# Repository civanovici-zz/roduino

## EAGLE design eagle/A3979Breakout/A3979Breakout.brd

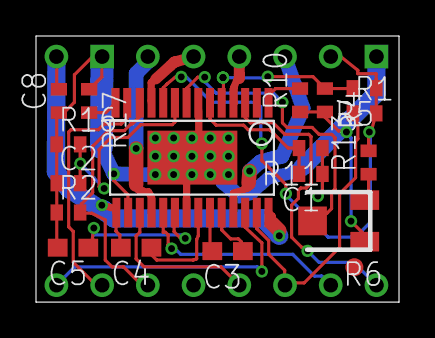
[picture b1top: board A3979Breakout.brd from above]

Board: 2 copper layers, 20.2 x 14.8 mm, 19 parts (0 on the bottom side), 25 nets.

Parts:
C1, C2: 680pF; C0402
C3, C4, C5: 0.22uF; C0603
C8: 0.1uF; C0402
E$1: FIDUCIAL_L10
IC1: A3979; TSSOP28
R1, R2, R5: 100K; R0402
R4: 47K; R0402
R6: RTRIM22AR
R10, R17: 0.2; R0402
R11, R16: 20K; R0402
R13: 2.7K; R0402
U$1: POLOLU_A4983CARRIER; A3979BREAKOUT

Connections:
1A: IC1.P$4, U$1.1A
1B: IC1.P$25, U$1.1B
2A: IC1.P$11, U$1.2A
2B: IC1.P$18, U$1.2B
+12V: C4.2, C8.2, IC1.P$15, IC1.P$28, U$1.VMOT
DIR: IC1.P$3, U$1.DIR
EN: IC1.P$26, U$1.EN
GND: C1.1, C2.1, C5.2, C8.1, IC1.P$7, IC1.P$16, IC1.P$21, IC1.P$29, R2.1, R4.2, R6.1, R10.1, R11.1, R16.1, R17.1, U$1.GND, U$1.GND@0
MS1: IC1.P$13, U$1.MS1
MS2: IC1.P$12, R2.2, U$1.MS2
unnamed: IC1.P$1, R10.2
unnamed: R6.3, R13.1
unnamed: IC1.P$14, R17.2
unnamed: IC1.P$5, R4.1, R5.2
unnamed: IC1.P$8, R6.2
unnamed: C1.2, IC1.P$6, R11.2
unnamed: C2.2, IC1.P$9, R16.2
unnamed: C3.1, IC1.P$24
unnamed: C3.2, IC1.P$23
unnamed: C4.1, IC1.P$22
unnamed: C5.1, IC1.P$20
RST: IC1.P$17, U$1.RST
SLP: IC1.P$27, R1.1, U$1.SLP
STP: IC1.P$19, U$1.STEP
VCC: IC1.P$10, R1.2, R5.1, R13.2, U$1.VDD

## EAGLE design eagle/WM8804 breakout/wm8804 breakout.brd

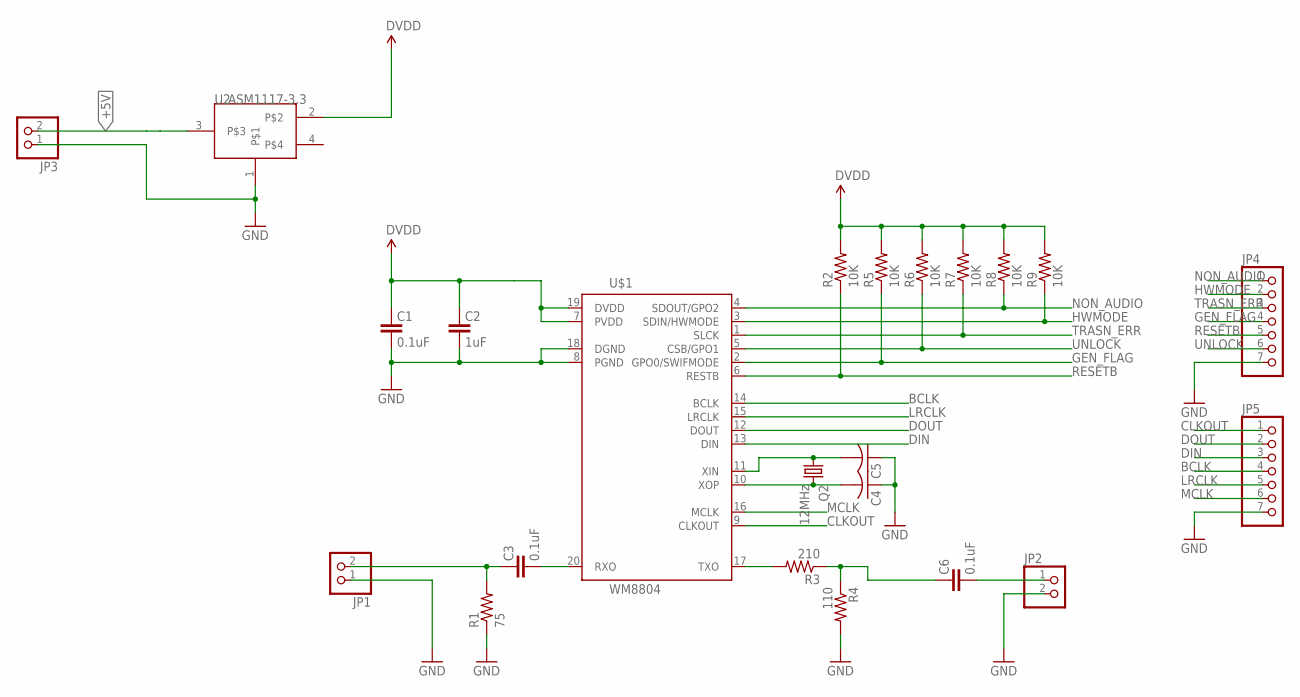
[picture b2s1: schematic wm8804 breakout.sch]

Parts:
C1, C3, C6: 0.1uF; 0805
C2: 1uF; 0805
C4, C5: C-USC0805; C0805
JP1, JP2, JP3: PINHD-1X2; 1X02
JP4, JP5: PINHD-1X7; 1X07
Q2: 12MHz; CTS406
R1: 75; 0805
R2, R5, R6, R7, R8, R9: 10K; 0805
R3: 210; 0805
R4: 110; 0805
U2: ASM1117-3.3; SOT223
U$1: WM8804; SSOP20

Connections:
+5V: JP3.2, U2.3
BCLK: JP5.4, U$1.14 (BCLK)
CLKOUT: JP5.1, U$1.9 (CLKOUT)
DIN: JP5.3, U$1.13 (DIN)
DOUT: JP5.2, U$1.12 (DOUT)
DVDD: C1.2, C2.2, R2.2, R5.2, R6.2, R7.2, R8.2, R9.2, U2.2, U$1.7 (PVDD), U$1.19 (DVDD)
GEN_FLAG: JP4.4, R5.1, U$1.2 (GPO0/SWIFMODE)
GND: C1.1, C2.1, C4.1, C5.1, JP1.1, JP2.2, JP3.1, JP4.7, JP5.7, R1.1, R4.2, U2.1, U$1.8 (PGND), U$1.18 (DGND)
HWMODE: JP4.2, R9.1, U$1.3 (SDIN/HWMODE)
LRCLK: JP5.5, U$1.15 (LRCLK)
MCLK: JP5.6, U$1.16 (MCLK)
unnamed: C5.2, Q2.1, U$1.11 (XIN)
unnamed: C4.2, Q2.3 (2), U$1.10 (XOP)
unnamed: C3.2, JP1.2, R1.2
unnamed: C3.1, U$1.20 (RXO)
unnamed: R3.2, U$1.17 (TXO)
unnamed: C6.2, R3.1, R4.1
unnamed: C6.1, JP2.1
NON_AUDIO: JP4.1, R8.1, U$1.4 (SDOUT/GPO2)
RESETB: JP4.5, R2.1, U$1.6 (RESTB)
TRASN_ERR: JP4.3, R7.1, U$1.1 (SLCK)
UNLOCK: JP4.6, R6.1, U$1.5 (CSB/GPO1)

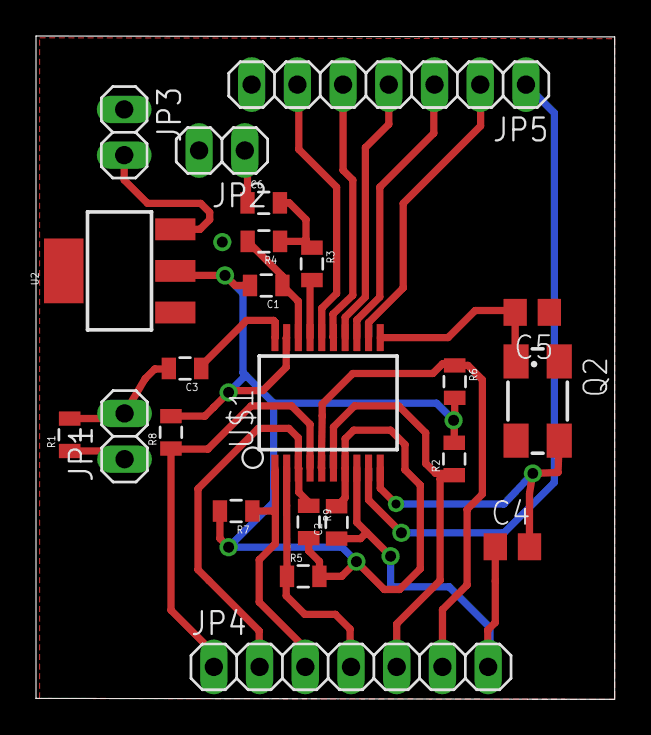
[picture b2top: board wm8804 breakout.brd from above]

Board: 2 copper layers, 32.1 x 36.8 mm, 23 parts (0 on the bottom side), 22 nets.

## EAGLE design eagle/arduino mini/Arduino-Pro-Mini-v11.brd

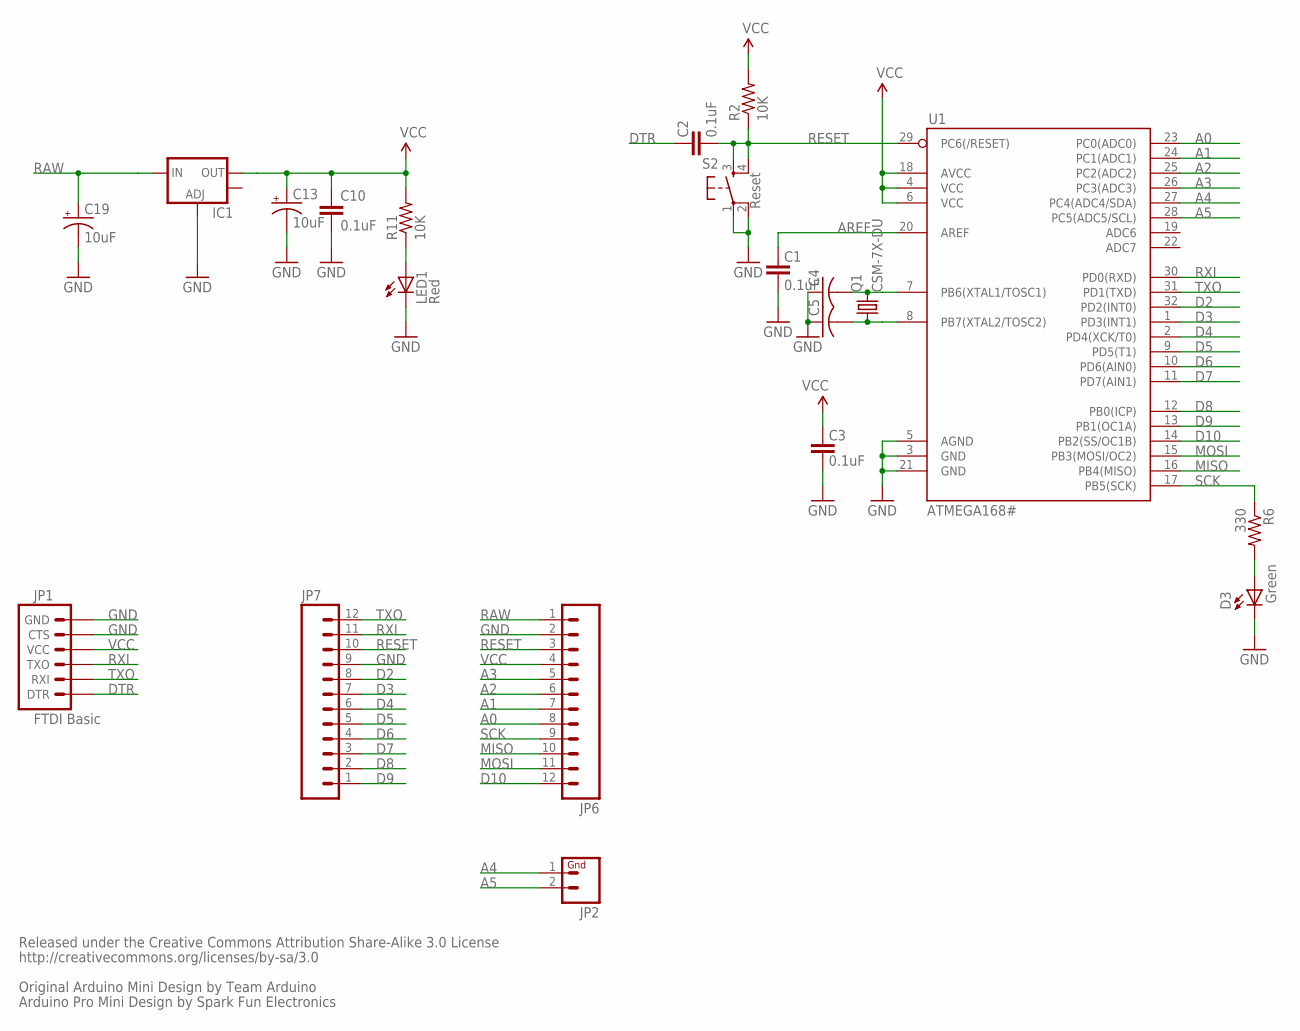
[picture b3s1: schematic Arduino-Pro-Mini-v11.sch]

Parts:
C1, C2, C3, C10: 0.1uF; 0805
C4, C5: C-USC0805; C0805
C13, C19: 10uF; EIA3216
D3: Green; LED-0603
IC1: V_REG_LM1117SOT223; SOT223
JP1: FTDI Basic; 1X06
JP2: M02PTH; 1X02
JP6, JP7: M12PTH; 1X12
LED1: Red; LED-0603
Q1: CSM-7X-DU
R2, R11: 10K; 0805
R6: 330; 0805
S2: Reset; TACTILE_SWITCH_SMD
U1: ATMEGA168#; TQFP32-08

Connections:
A0: JP6.8, U1.23 (PC0(ADC0))
A1: JP6.7, U1.24 (PC1(ADC1))
A2: JP6.6, U1.25 (PC2(ADC2))
A3: JP6.5, U1.26 (PC3(ADC3))
A4: JP2.1, U1.27 (PC4(ADC4/SDA))
A5: JP2.2, U1.28 (PC5(ADC5/SCL))
AREF: C1.2, U1.20 (AREF)
D2: JP7.8, U1.32 (PD2(INT0))
D3: JP7.7, U1.1 (PD3(INT1))
D4: JP7.6, U1.2 (PD4(XCK/T0))
D5: JP7.5, U1.9 (PD5(T1))
D6: JP7.4, U1.10 (PD6(AIN0))
D7: JP7.3, U1.11 (PD7(AIN1))
D8: JP7.2, U1.12 (PB0(ICP))
D9: JP7.1, U1.13 (PB1(OC1A))
D10: JP6.12, U1.14 (PB2(SS/OC1B))
DTR: C2.2, JP1.1 (DTR)
GND: C1.1, C3.1, C4.1, C5.1, C10.2, C13.C (-), C19.C (-), D3.C, IC1.1 (ADJ), JP1.5 (CTS), JP1.6 (GND), JP6.2, JP7.9, LED1.C, S2.1, S2.2, U1.3 (GND), U1.5 (AGND), U1.21 (GND)
MISO: JP6.10, U1.16 (PB4(MISO))
MOSI: JP6.11, U1.15 (PB3(MOSI/OC2))
unnamed: C5.2, Q1.1, U1.8 (PB7(XTAL2/TOSC2))
unnamed: C4.2, Q1.2, U1.7 (PB6(XTAL1/TOSC1))
unnamed: D3.A, R6.2
unnamed: LED1.A, R11.1
RAW: C19.A (+), IC1.3 (IN), JP6.1
RESET: C2.1, JP6.3, JP7.10, R2.1, S2.3, S2.4, U1.29 (PC6(/RESET))
RXI: JP1.3 (TXO), JP7.11, U1.30 (PD0(RXD))
SCK: JP6.9, R6.1, U1.17 (PB5(SCK))
TXO: JP1.2 (RXI), JP7.12, U1.31 (PD1(TXD))
VCC: C3.2, C10.1, C13.A (+), IC1.2 (OUT), JP1.4 (VCC), JP6.4, R2.2, R11.2, U1.4 (VCC), U1.6 (VCC), U1.18 (AVCC)

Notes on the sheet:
Released under the Creative Commons Attribution Share-Alike 3.0 License
http://creativecommons.org/licenses/by-sa/3.0
Original Arduino Mini Design by Team Arduino
Arduino Pro Mini Design by Spark Fun Electronics

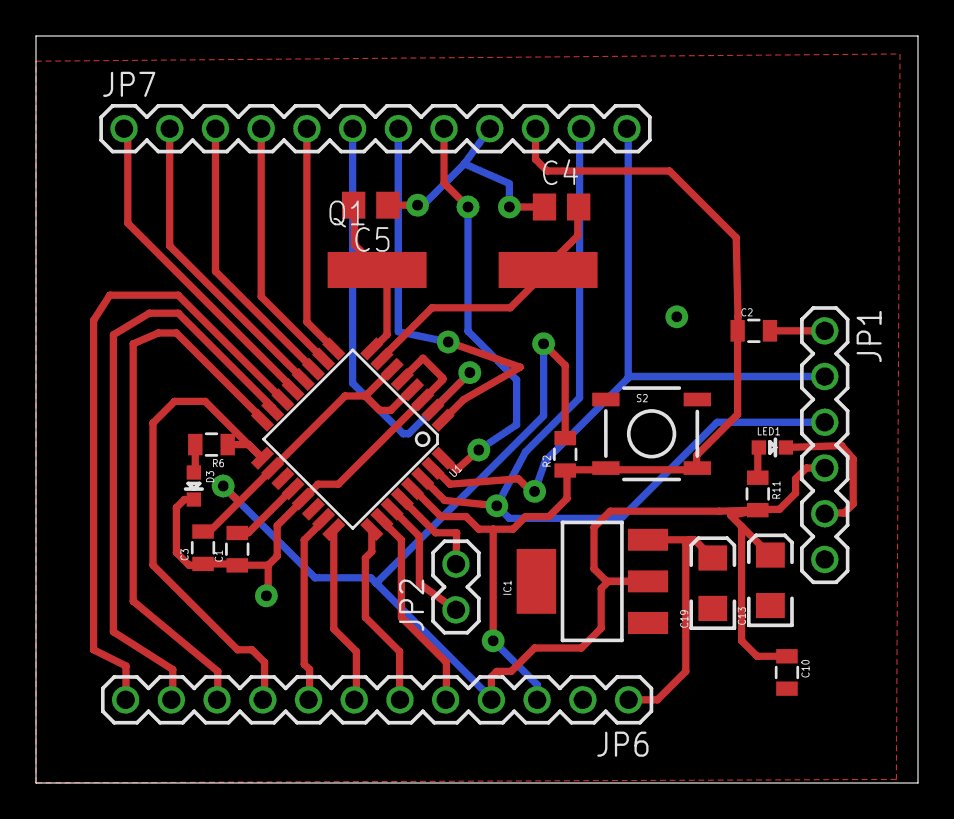
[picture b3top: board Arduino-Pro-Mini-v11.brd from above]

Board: 2 copper layers, 49.0 x 41.5 mm, 21 parts (0 on the bottom side), 30 nets.

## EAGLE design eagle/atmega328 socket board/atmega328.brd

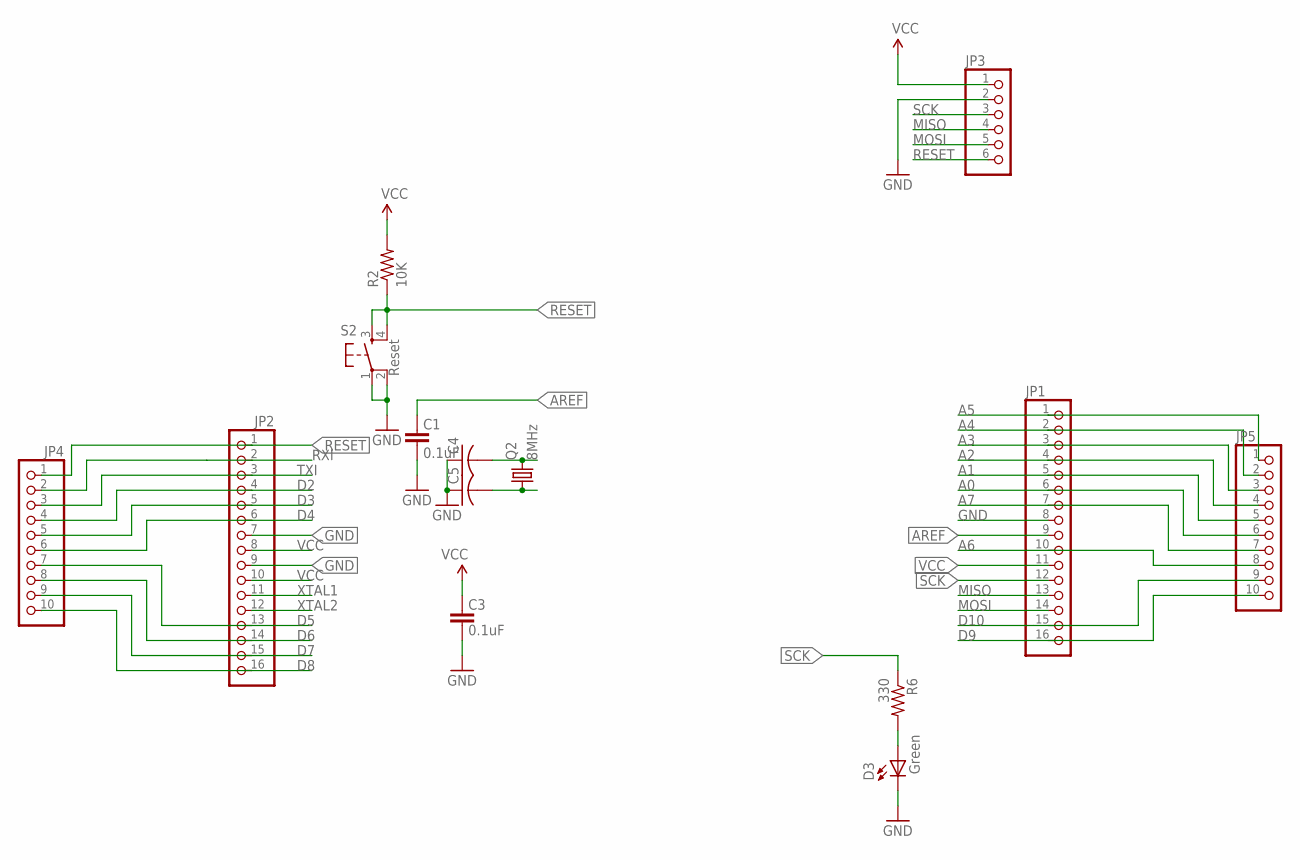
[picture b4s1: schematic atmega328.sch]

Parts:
C1, C3: 0.1uF; 0805
C4, C5: C-USC0805; C0805
D3: Green; LED-0603
JP1, JP2: PINHD-1X16; 1X16
JP3: PINHD-1X6; 1X06
JP4, JP5: PINHD-1X10; 1X10
Q2: 8MHz; CTS406
R2: 10K; 0805
R6: 330; 0805
S2: Reset; TACTILE_SWITCH_SMD

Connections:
A0: JP1.6, JP5.6
A1: JP1.5, JP5.5
A2: JP1.4, JP5.4
A3: JP1.3, JP5.3
A4: JP1.2, JP5.2
A5: JP1.1, JP5.1
A6: JP1.10, JP5.8
A7: JP1.7, JP5.7
AREF: C1.2, JP1.9
D2: JP2.4, JP4.4
D3: JP2.5, JP4.5
D4: JP2.6, JP4.6
D5: JP2.13, JP4.7
D6: JP2.14, JP4.8
D7: JP2.15, JP4.9
D8: JP2.16, JP4.10
D9: JP1.16, JP5.10
D10: JP1.15, JP5.9
GND: C1.1, C3.1, C4.1, C5.1, D3.C, JP1.8, JP2.7, JP2.9, JP3.2, S2.1, S2.2
MISO: JP1.13, JP3.4
MOSI: JP1.14, JP3.5
unnamed: D3.A, R6.2
RESET: JP2.1, JP3.6, JP4.1, R2.1, S2.3, S2.4
RXI: JP2.2, JP4.2
SCK: JP1.12, JP3.3, R6.1
TXI: JP2.3, JP4.3
VCC: C3.2, JP1.11, JP2.8, JP2.10, JP3.1, R2.2
XTAL1: C4.2, JP2.11, Q2.3 (2)
XTAL2: C5.2, JP2.12, Q2.1

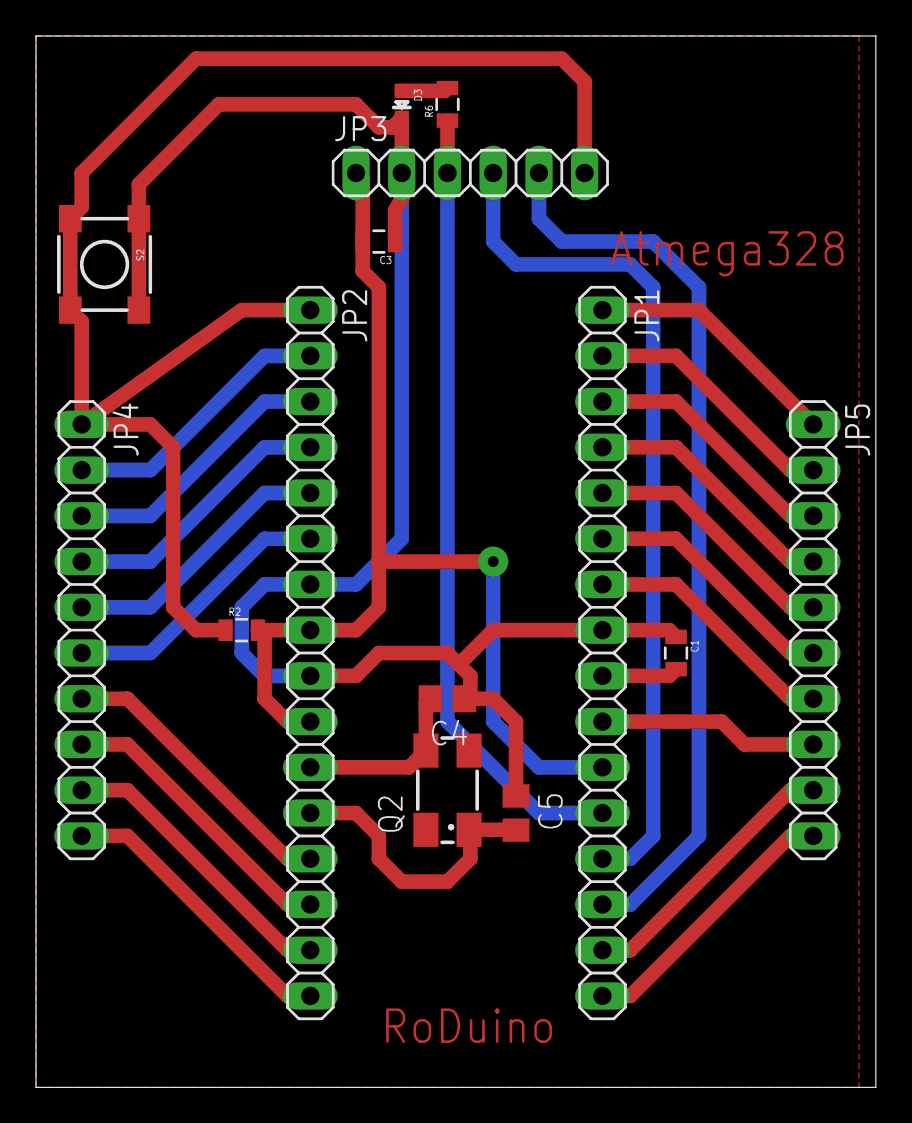
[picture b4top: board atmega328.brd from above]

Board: 2 copper layers, 46.7 x 58.4 mm, 14 parts (0 on the bottom side), 29 nets.

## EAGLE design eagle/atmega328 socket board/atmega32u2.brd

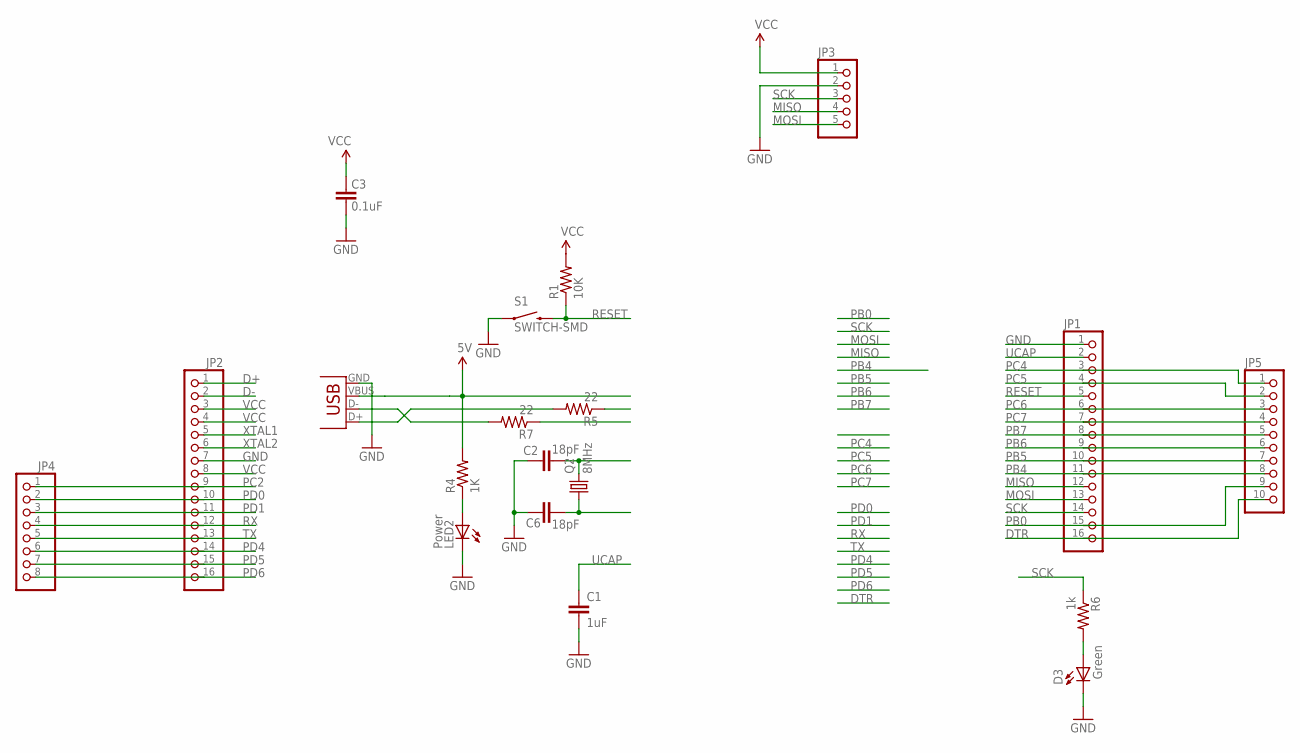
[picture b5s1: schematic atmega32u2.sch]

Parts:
C1: 1uF; 0402-CAP
C2, C6: 18pF; 0402-CAP
C3: 0.1uF; 0805
D3: Green; LED-0603
JP1, JP2: PINHD-1X16; 1X16
JP3: PINHD-1X5; 1X05
JP4: PINHD-1X8; 1X08
JP5: PINHD-1X10; 1X10
LED2: Power; LED-0603
Q2: 8MHz; CTS406
R1: 10K; 0805
R4: 1K; 0805
R5, R7: 22; 0805
R6: 1k; 0805
S1: SWITCH-SMD; TACTILE_SWITCH_SMD
X1: USBSMD; USB-MINIB

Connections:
D+: JP2.1, R5.1
D-: JP2.2, R7.1
DTR: JP1.16, JP5.10
GND: C1.2, C2.2, C3.1, C6.2, D3.C, JP1.1, JP2.7, JP3.2, LED2.C, S1.1, X1.GND
MISO: JP1.12, JP3.4
MOSI: JP1.13, JP3.5
unnamed: LED2.A, R4.1
unnamed: R5.2, X1.D+
unnamed: R7.2, X1.D-
unnamed: D3.A, R6.2
PB0: JP1.15, JP5.9
PB4: JP1.11, JP5.8
PB5: JP1.10, JP5.7
PB6: JP1.9, JP5.6
PB7: JP1.8, JP5.5
PC2: JP2.9, JP4.1
PC4: JP1.3, JP5.1
PC5: JP1.4, JP5.2
PC6: JP1.6, JP5.3
PC7: JP1.7, JP5.4
PD0: JP2.10, JP4.2
PD1: JP2.11, JP4.3
PD4: JP2.14, JP4.6
PD5: JP2.15, JP4.7
PD6: JP2.16, JP4.8
RESET: JP1.5, R1.1, S1.3 (2)
RX: JP2.12, JP4.4
SCK: JP1.14, JP3.3, R6.1
TX: JP2.13, JP4.5
UCAP: C1.1, JP1.2
VCC: C3.2, JP2.3, JP2.4, JP2.8, JP3.1, R1.2, R4.2, X1.VBUS
XTAL1: C2.1, JP2.5, Q2.3 (2)
XTAL2: C6.1, JP2.6, Q2.1

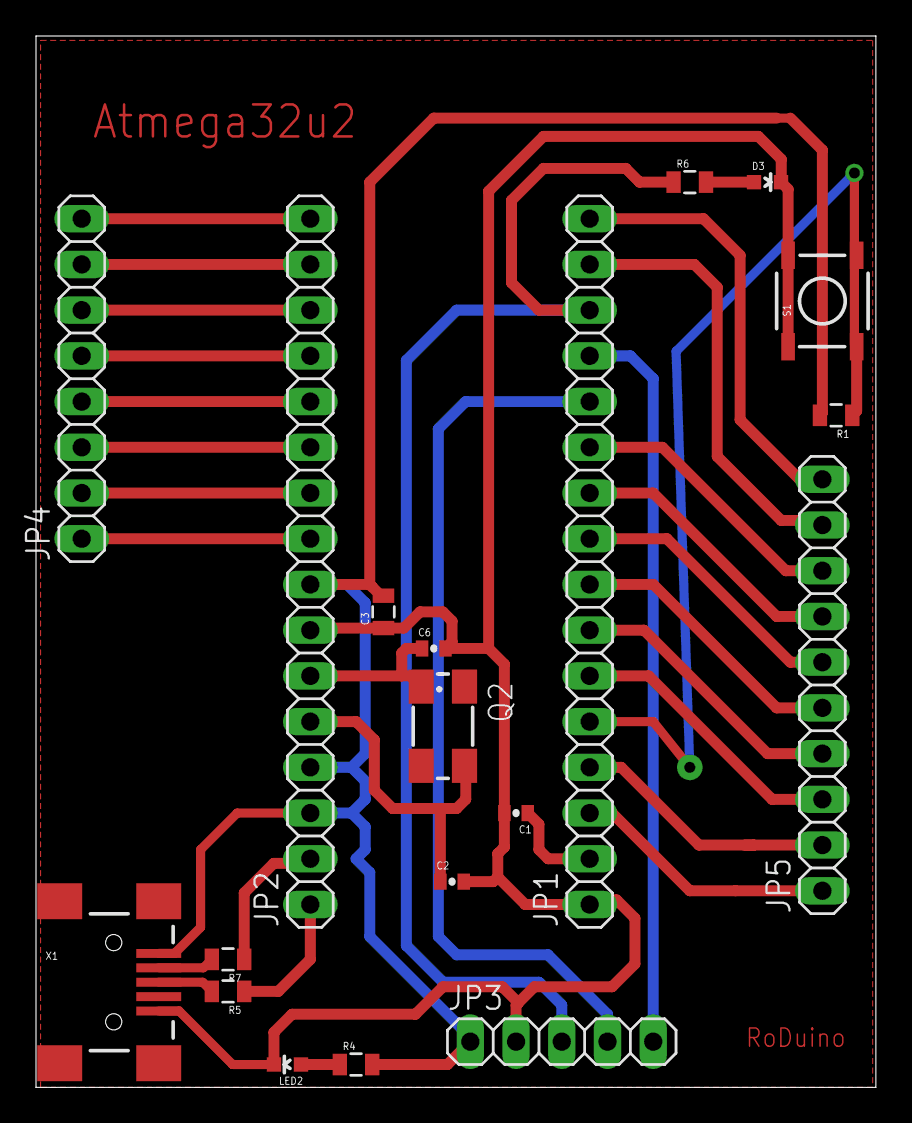
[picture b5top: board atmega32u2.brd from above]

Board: 2 copper layers, 46.7 x 58.4 mm, 19 parts (0 on the bottom side), 33 nets.
